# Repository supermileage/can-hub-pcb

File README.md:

# Controller Area Network hub PCB

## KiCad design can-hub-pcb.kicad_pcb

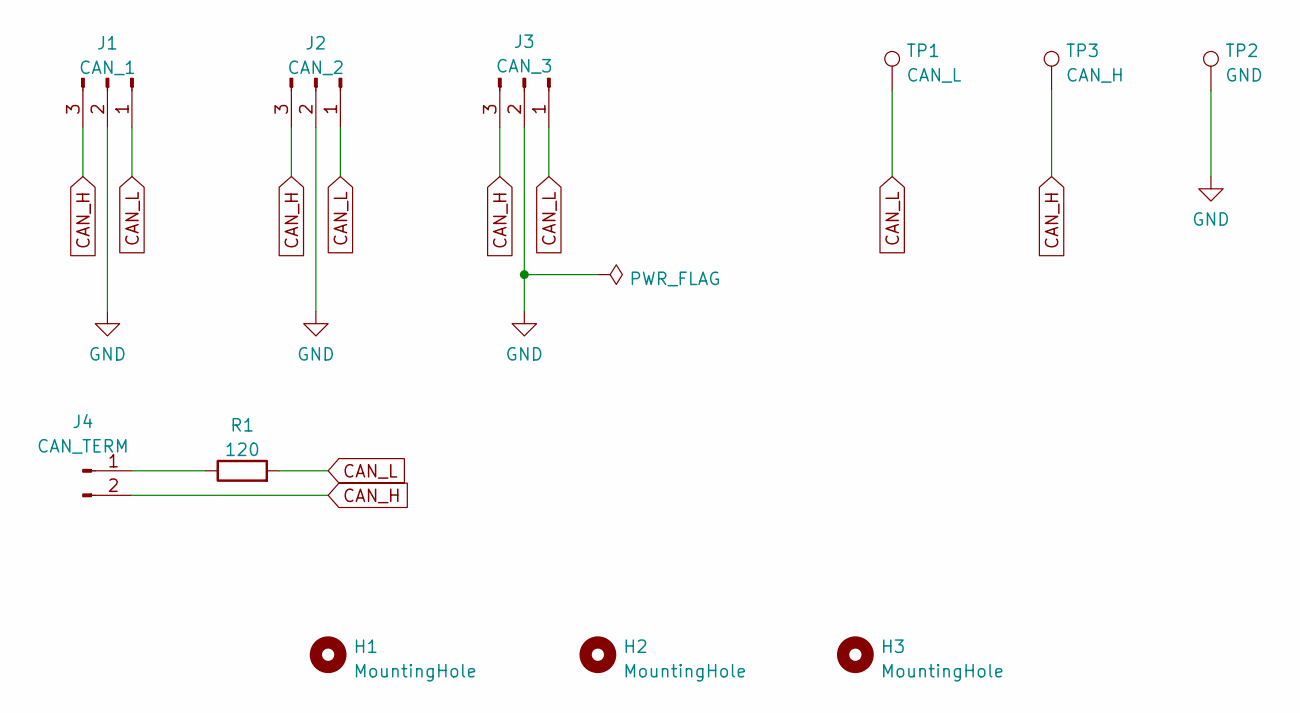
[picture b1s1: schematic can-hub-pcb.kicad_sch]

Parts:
H1, H2, H3: MountingHole; MountingHole_3.2mm_M3
J1: CAN_1; 705510002
J2: CAN_2; 705510002
J3: CAN_3; 705510002
J4: CAN_TERM; PinHeader_1x02_P2.54mm_Vertical
R1: 120; R_0805_2012Metric
TP1: CAN_L; TestPoint_Pad_1.0x1.0mm
TP2: GND; TestPoint_Pad_1.0x1.0mm
TP3: CAN_H; TestPoint_Pad_1.0x1.0mm

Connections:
CAN_H: J1.3, J2.3, J3.3, J4.2, TP3.1
CAN_L: J1.1, J2.1, J3.1, R1.2, TP1.1
GND: J1.2, J2.2, J3.2, TP2.1
unnamed: J4.1, R1.1

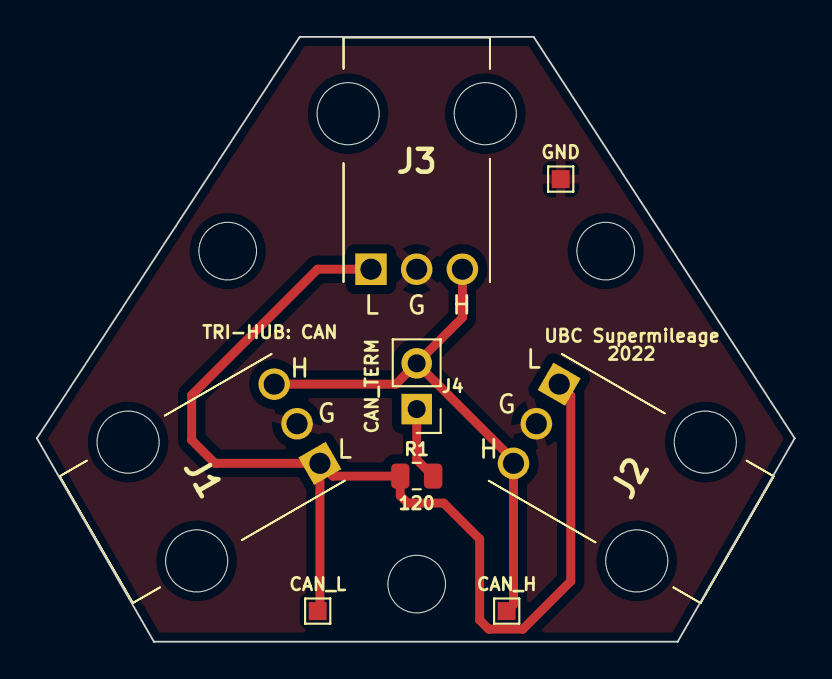
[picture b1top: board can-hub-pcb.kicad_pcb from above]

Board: 2 copper layers, 42.1 x 33.6 mm, 11 parts (0 on the bottom side), 4 nets.

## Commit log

2022-11-12 adds readme
2022-11-12 completes schematic and layout
2022-12-03 finishes PCB and exports output
